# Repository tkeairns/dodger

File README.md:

# dodger
Let's see how far along I go with this project

## Overview 
Building on the Stanford Pupper project with a Jetson Nano instead of a Raspberry Pi

## Lidar
If using Garmin's lidarlite_v3 module, build the shared object locally with:

```bazel build //dodger:libdodger.so```

## Docs 
Build python docs with:

```make docs```

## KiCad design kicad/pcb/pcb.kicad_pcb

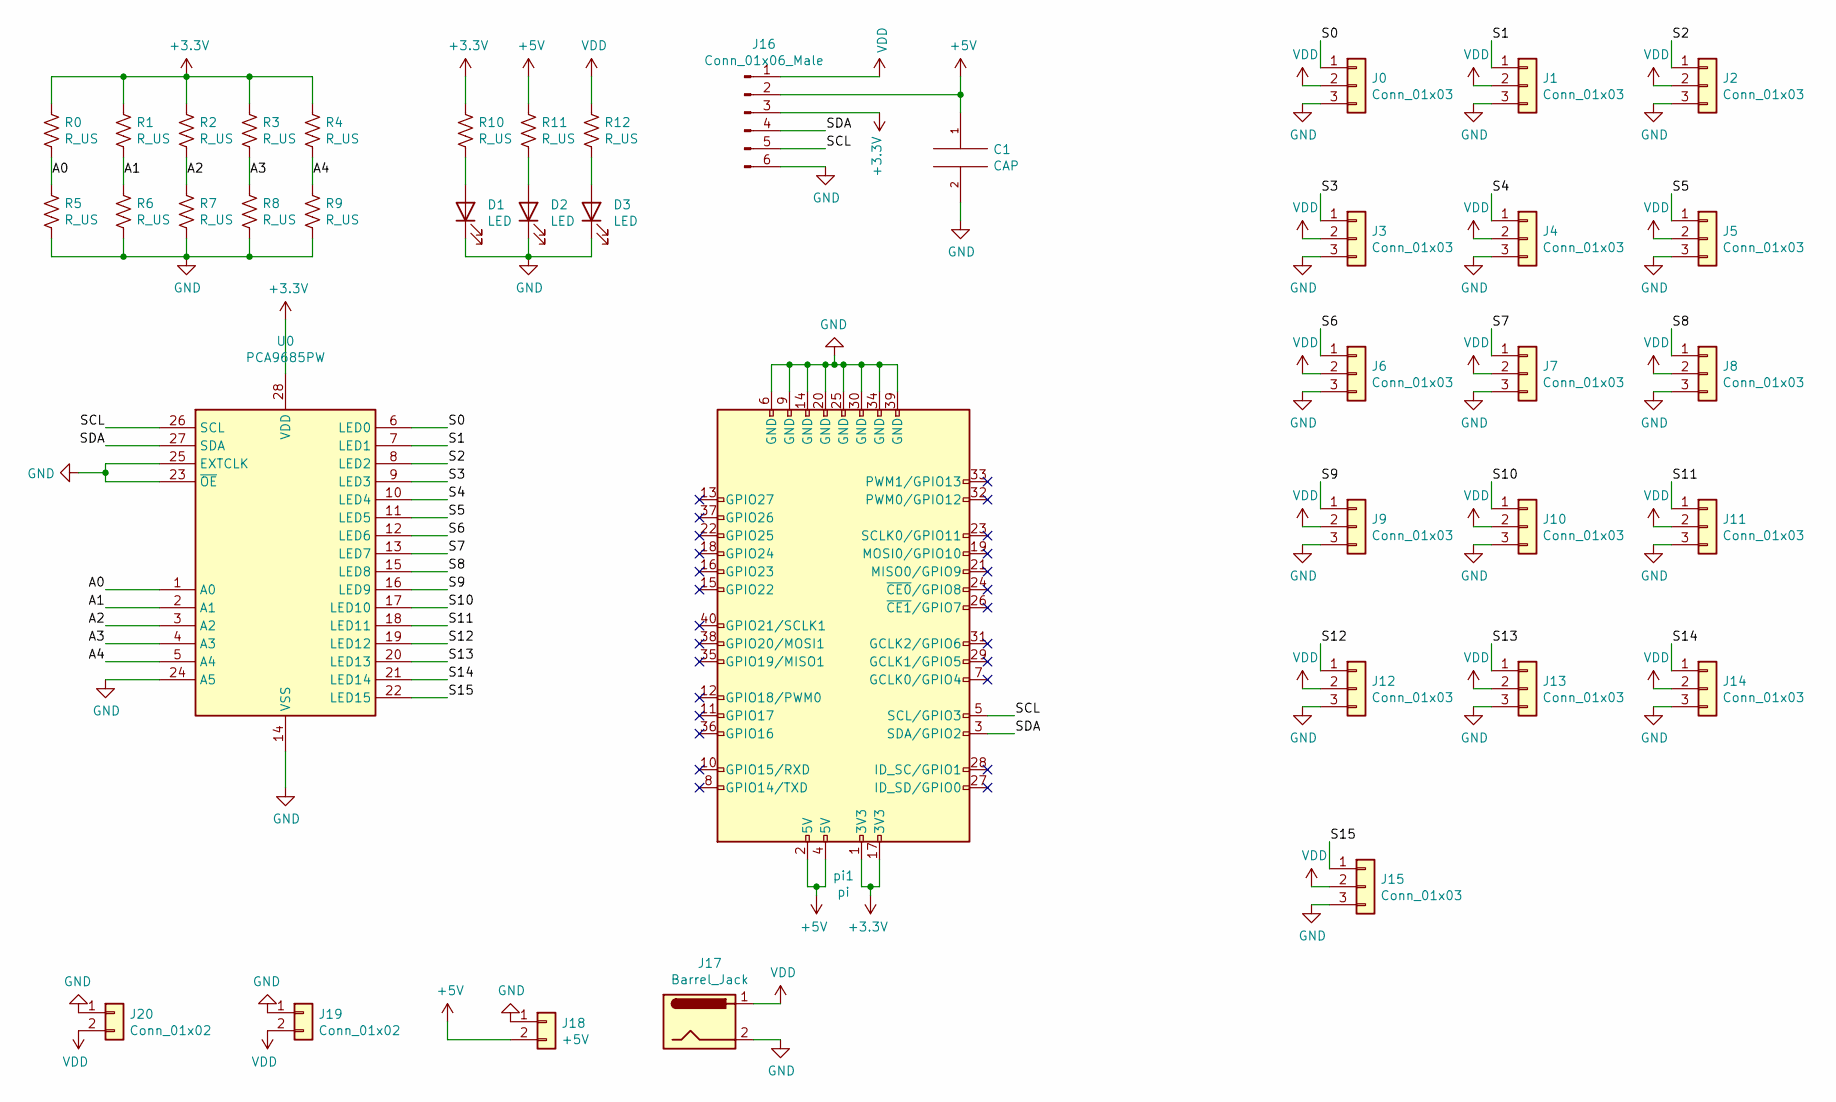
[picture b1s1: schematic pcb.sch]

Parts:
C1: CAP; CP_Radial_D10.0mm_P5.00mm
D1, D2, D3: LED; LED_0805_2012Metric_Pad1.15x1.40mm_HandSolder
J0, J1, J2, J3, J4, J5, J6, J7, J8, J9, J10, J11, J12, J13, J14, J15: Conn_01x03; PinHeader_1x03_P2.54mm_Vertical
J16: Conn_01x06_Male; PinHeader_1x06_P2.54mm_Vertical
J17: Barrel_Jack; BarrelJack_Horizontal
J18: +5V; PinHeader_1x02_P2.54mm_Vertical
J19: Conn_01x02; PinHeader_1x02_P2.54mm_Vertical
J20: Conn_01x02; AMASS_XT60-M_1x02_P7.20mm_Vertical
R0, R1, R2, R3, R4, R5, R6, R7, R8, R9, R10, R11, R12: R_US; R_0805_2012Metric_Pad1.15x1.40mm_HandSolder
U0: PCA9685PW; TSSOP-28_4.4x9.7mm_P0.65mm
pi1: pi; PinSocket_2x20_P2.54mm_Vertical

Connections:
+3V3: J16.3, R0.1, R1.1, R2.1, R3.1, R4.1, R10.1, U0.28 (VDD), pi1.1 (3V3), pi1.17 (3V3)
+5V: C1.1, J16.2, J18.2, R11.1, pi1.2 (5V), pi1.4 (5V)
/A0: R0.2, R5.1, U0.1 (A0)
/A1: R1.2, R6.1, U0.2 (A1)
/A2: R2.2, R7.1, U0.3 (A2)
/A3: R3.2, R8.1, U0.4 (A3)
/A4: R4.2, R9.1, U0.5 (A4)
/S0: J0.1, U0.6 (LED0)
/S1: J1.1, U0.7 (LED1)
/S2: J2.1, U0.8 (LED2)
/S3: J3.1, U0.9 (LED3)
/S4: J4.1, U0.10 (LED4)
/S5: J5.1, U0.11 (LED5)
/S6: J6.1, U0.12 (LED6)
/S7: J7.1, U0.13 (LED7)
/S8: J8.1, U0.15 (LED8)
/S9: J9.1, U0.16 (LED9)
/S10: J10.1, U0.17 (LED10)
/S11: J11.1, U0.18 (LED11)
/S12: J12.1, U0.19 (LED12)
/S13: J13.1, U0.20 (LED13)
/S14: J14.1, U0.21 (LED14)
/S15: J15.1, U0.22 (LED15)
/SCL: J16.5, U0.26 (SCL), pi1.5 (SCL/GPIO3)
/SDA: J16.4, U0.27 (SDA), pi1.3 (SDA/GPIO2)
GND: C1.2, D1.1 (K), D2.1 (K), D3.1 (K), J0.3, J1.3, J2.3, J3.3, J4.3, J5.3, J6.3, J7.3, J8.3, J9.3, J10.3, J11.3, J12.3, J13.3, J14.3, J15.3, J16.6, J17.2, J18.1, J19.1, J20.1, R5.2, R6.2, R7.2, R8.2, R9.2, U0.14 (VSS), U0.23 (~OE), U0.24 (A5), U0.25 (EXTCLK), pi1.6 (GND), pi1.9 (GND), pi1.14 (GND), pi1.20 (GND), pi1.25 (GND), pi1.30 (GND), pi1.34 (GND), pi1.39 (GND)
unnamed: D1.2 (A), R10.2
unnamed: D2.2 (A), R11.2
unnamed: D3.2 (A), R12.2
VDD: J0.2, J1.2, J2.2, J3.2, J4.2, J5.2, J6.2, J7.2, J8.2, J9.2, J10.2, J11.2, J12.2, J13.2, J14.2, J15.2, J16.1, J17.1, J19.2, J20.2, R12.1

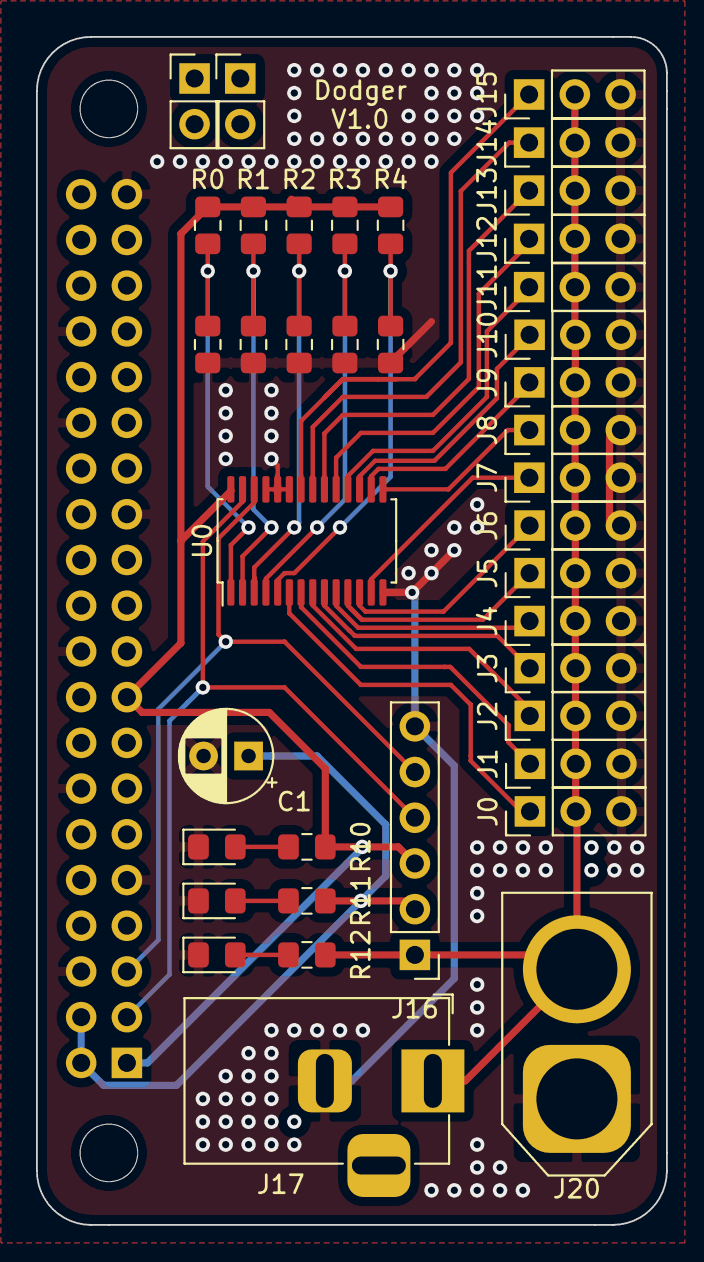
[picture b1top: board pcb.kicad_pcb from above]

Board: 2 copper layers, 35.0 x 66.0 mm, 42 parts (1 on the bottom side), 30 nets.

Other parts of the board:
J_POE0, J_POE2: Conn_01x02_Female; PinHeader_1x02_P2.54mm_Vertical
M3_bottom, M3_top: MountingHole_3.2mm_M3

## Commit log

2020-05-18 Added python cookiecutter
2020-05-18 Build python docs locally with 'make docs'
2020-05-18 Lidar LPF and 10ms polling
2020-05-24 Lidar methods and periodic. Open close base class
2020-05-30 Setting up camera
2020-06-08 Cleaning up submodules
2020-06-27 Kicad v1.0
2021-11-15 Bump pip from 19.2.3 to 21.1
    Bumps [pip](https://github.com/pypa/pip) from 19.2.3 to 21.1.
    - [Release notes](https://github.com/pypa/pip/releases)
    - [Changelog](https://github.com/pypa/pip/blob/main/NEWS.rst)
    - [Commits](https://github.com/pypa/pip/compare/19.2.3...21.1)
    ---
    updated-dependencies:
2022-12-26 Bump wheel from 0.33.6 to 0.38.1
    Bumps [wheel](https://github.com/pypa/wheel) from 0.33.6 to 0.38.1.
    - [Release notes](https://github.com/pypa/wheel/releases)
    - [Changelog](https://github.com/pypa/wheel/blob/main/docs/news.rst)
    - [Commits](https://github.com/pypa/wheel/compare/0.33.6...0.38.1)
    ---
    updated-dependencies:
